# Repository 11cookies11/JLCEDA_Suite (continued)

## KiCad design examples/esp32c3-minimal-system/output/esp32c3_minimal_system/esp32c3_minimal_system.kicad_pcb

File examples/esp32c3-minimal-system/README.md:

# ESP32-C3 Minimal System

Verified example for the current KiCad Agent Suite project protocol.

This project models an ESP32-C3 minimum system board with 5 V input, 3.3 V
regulation, USB-C power and data, boot and reset controls, status LED, and GPIO
expansion headers.

## Source Of Truth

Edit this file only:

```text
source/circuit-model.source.json
```

Generated files are kept for inspection and KiCad handoff:

```text
output/esp32c3_minimal_system/
```

Do not edit generated `build/`, `output/`, or `project.state.json` files manually.

## Rebuild

Run from this example directory:

```powershell
hwtool agent status --project .
hwtool agent inspect --project .
hwtool agent resolve-symbols --project . --timeout 120
hwtool agent build-ir --project .
hwtool agent validate-ir --project .
hwtool agent export-kicad --project .
hwtool agent report --project . --markdown
hwtool agent diagnose --project .
```

## Current Verification

- `build-ir`: 17 components, 8 nets
- `validate-ir`: ok, 0 errors, 0 warnings
- `export-kicad`: generated schematic, PCB, ERC, and report artifacts
- `diagnose`: no must-fix issues

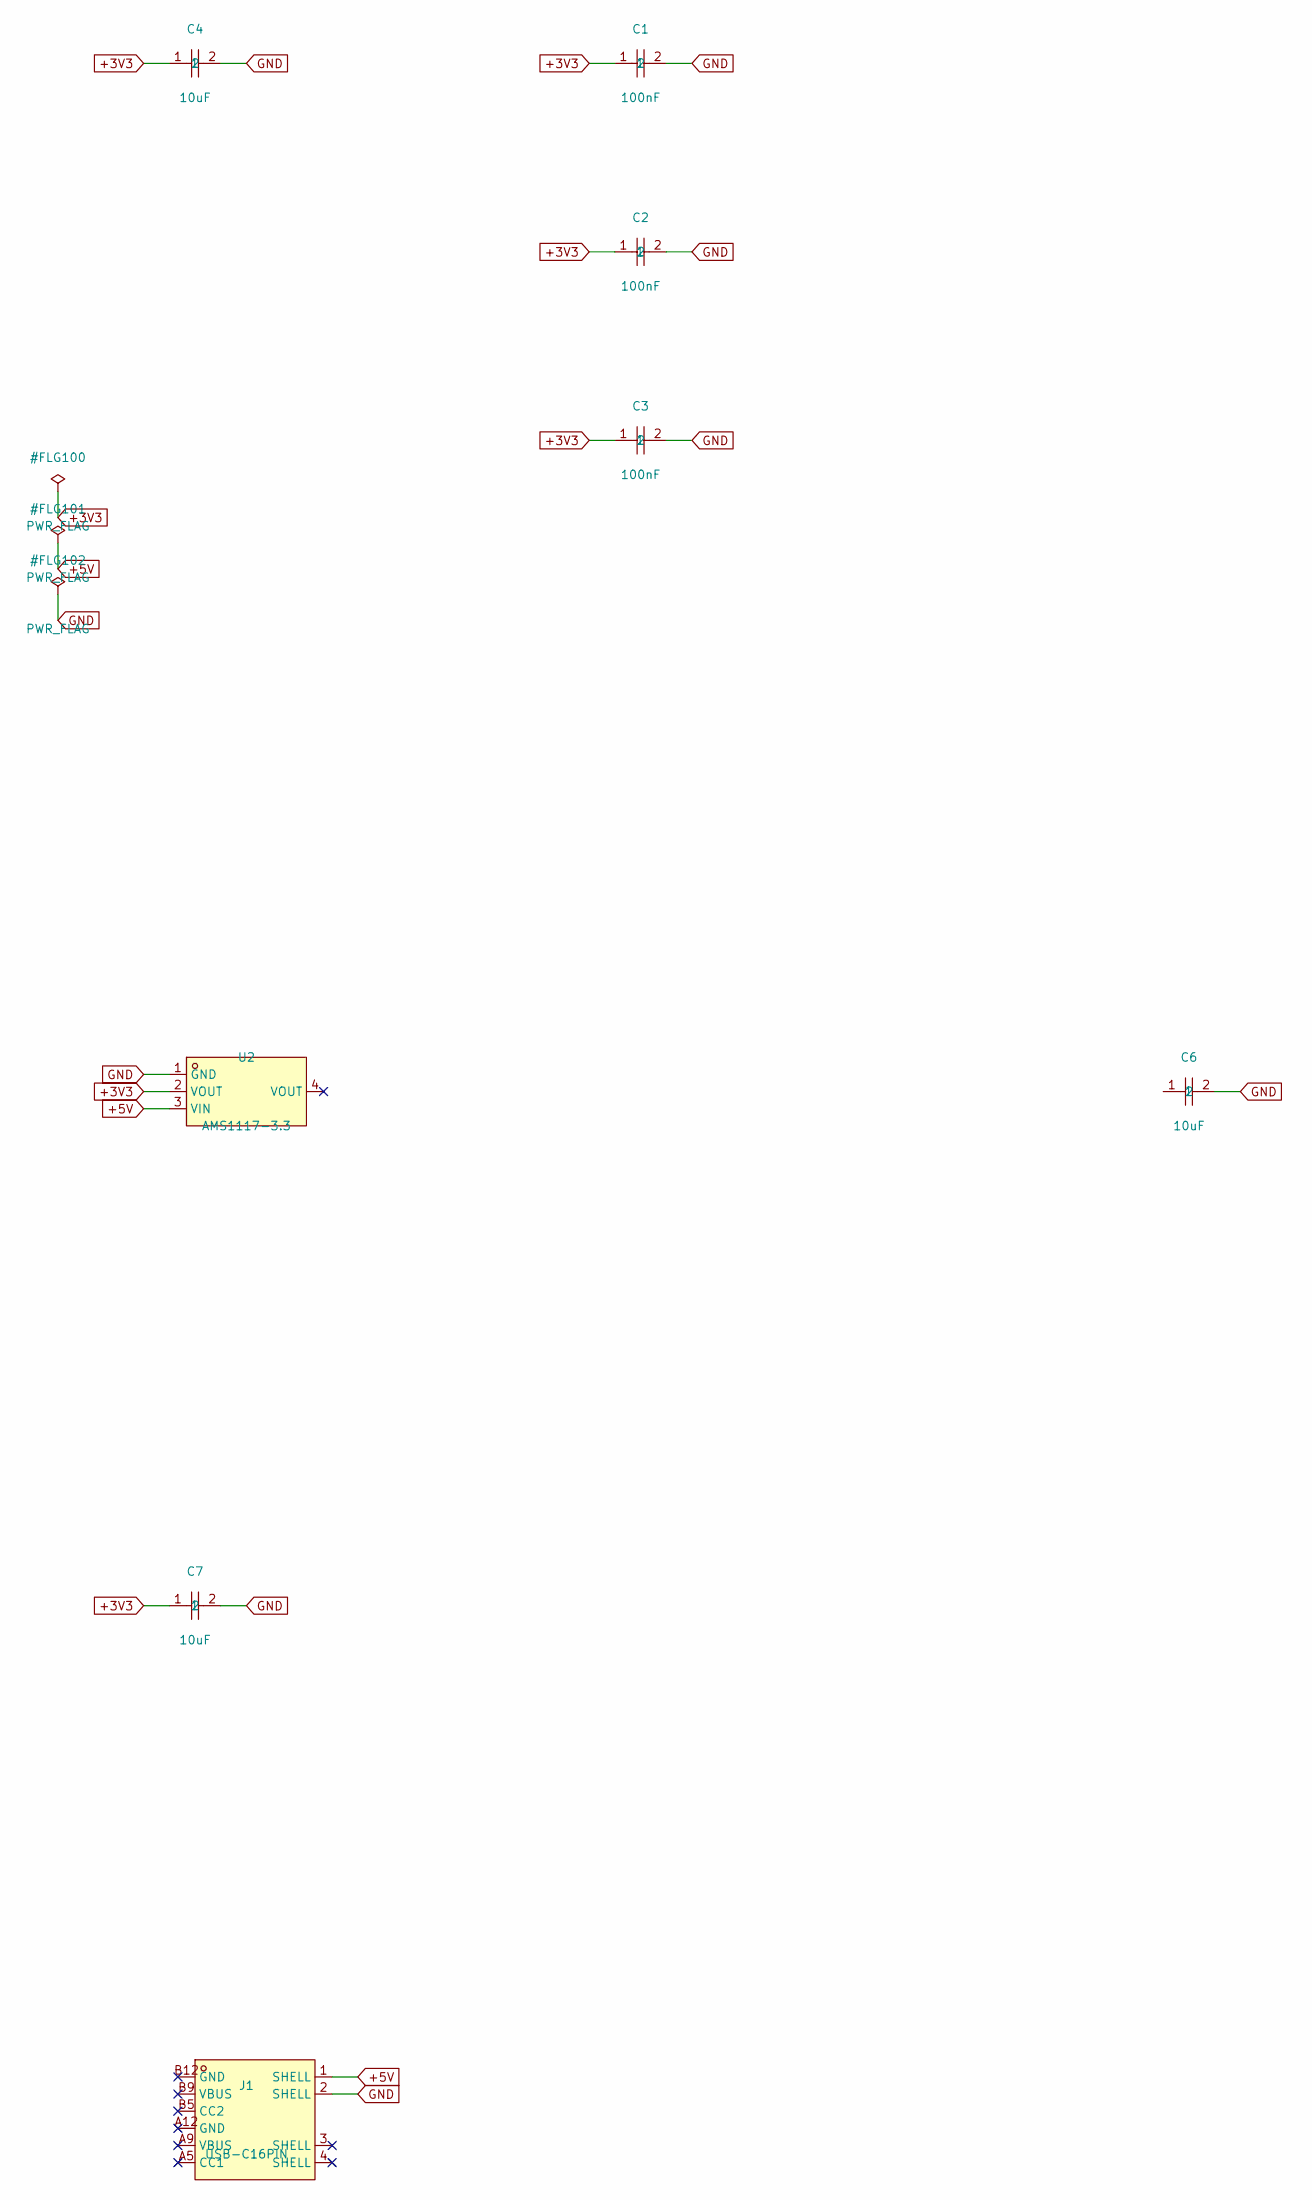
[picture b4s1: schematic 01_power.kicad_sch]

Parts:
C1, C2, C3: 100nF; C0603; LCSC C1590
C4, C6, C7: 10uF; C0805; LCSC C1713
J1: USB-C16PIN; USB-C-SMD_USB-TYPE-C-006; LCSC C2927026
U2: AMS1117-3.3; SOT-223-3_L6.5-W3.4-P2.30-LS7.0-BR; LCSC C6186

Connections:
+3V3: C1.1, C2.1, C3.1, C4.1, C7.1, U2.2 (VOUT); also elsewhere on the board
+5V: J1.1 (SHELL), U2.3 (VIN)
GND: C1.2, C2.2, C3.2, C4.2, C6.2, C7.2, J1.2 (SHELL), U2.1 (GND); also elsewhere on the board

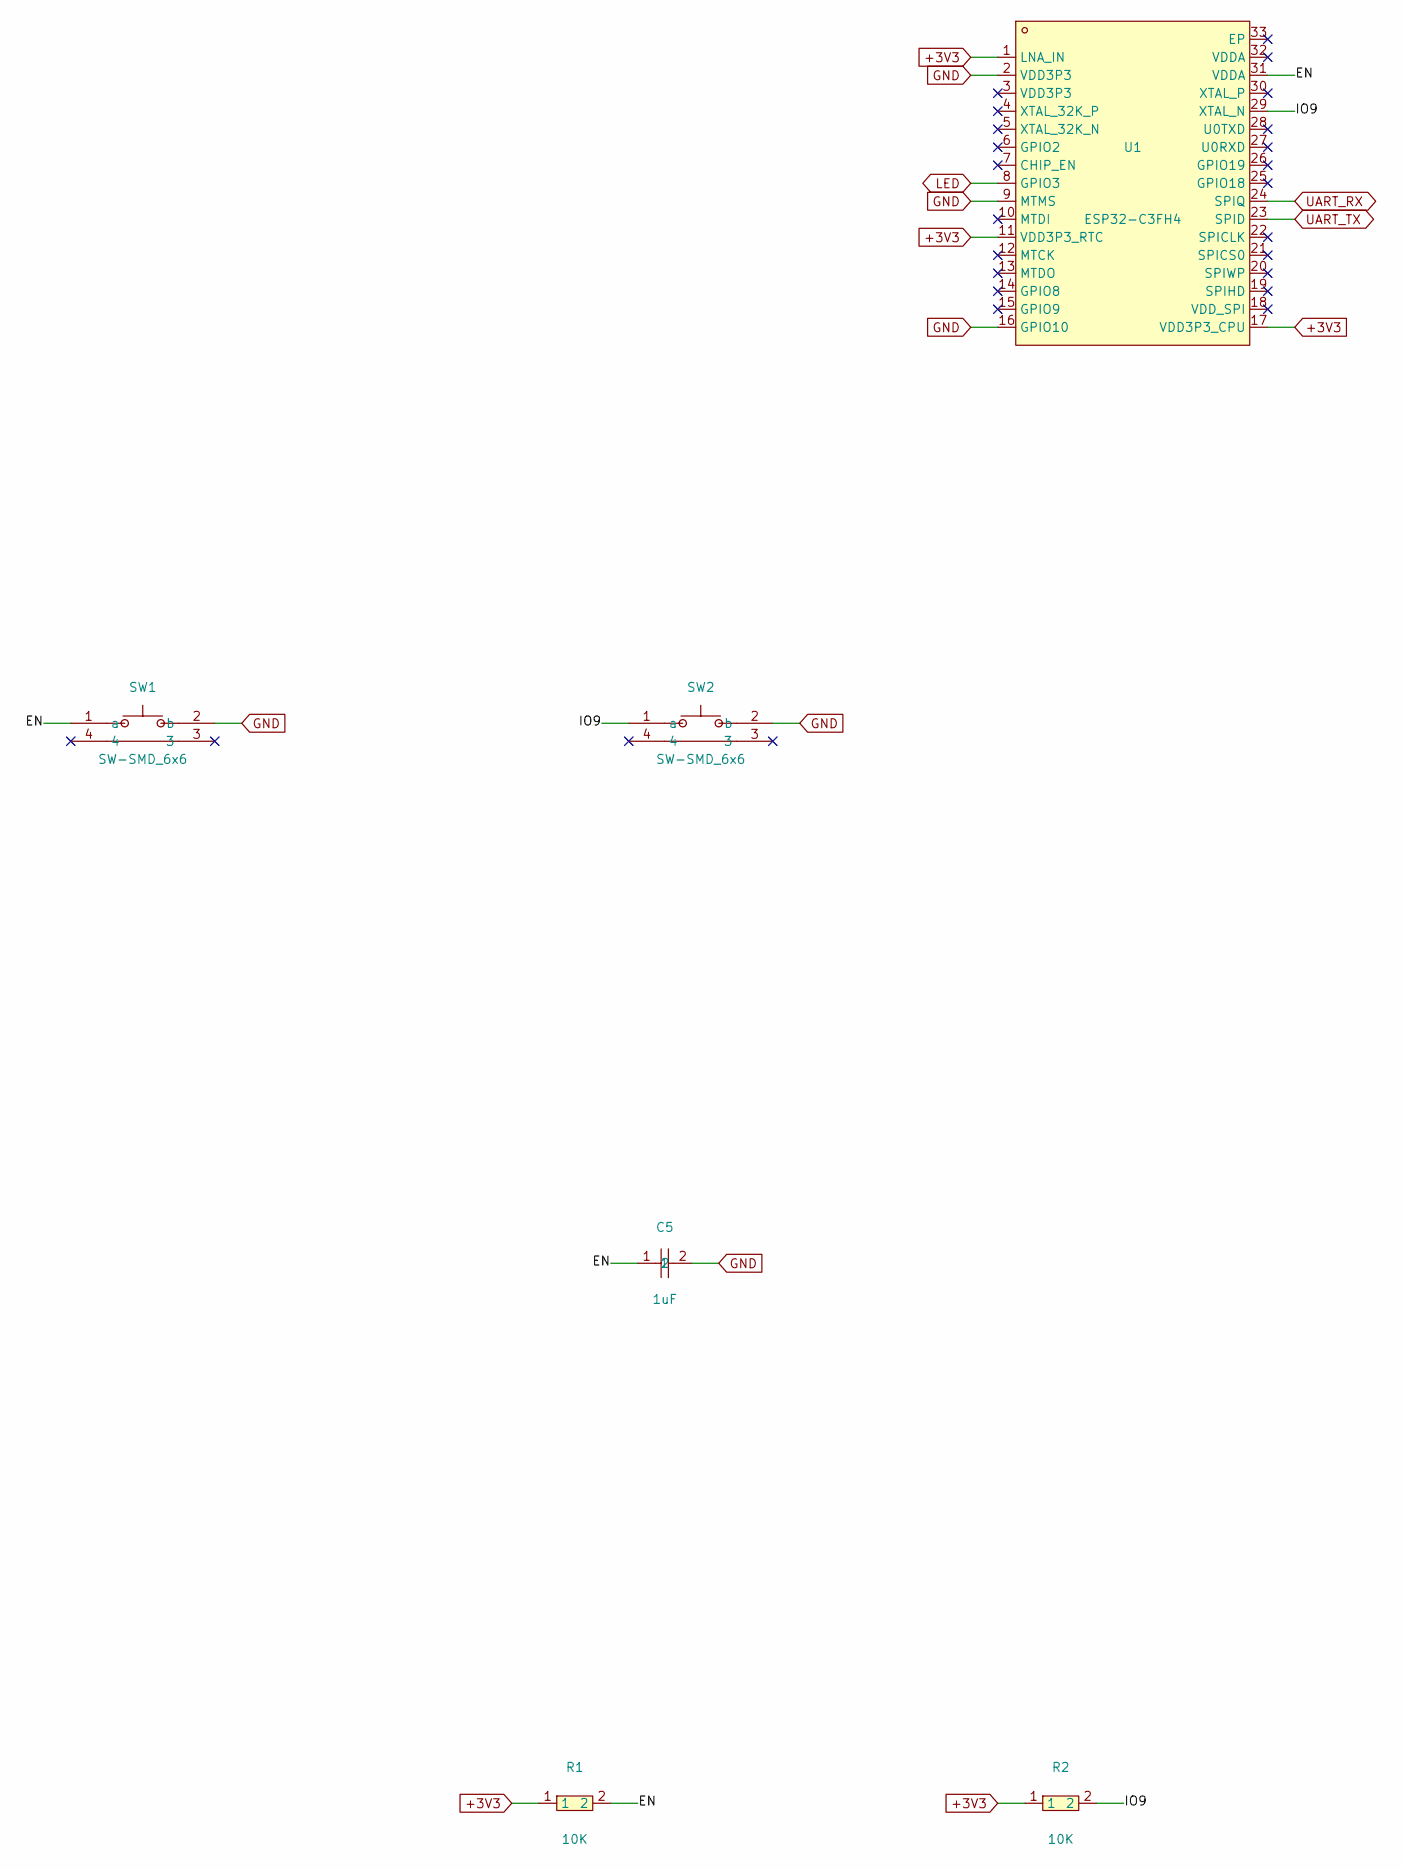
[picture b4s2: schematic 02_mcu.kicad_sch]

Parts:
C5: 1uF; C0603; LCSC C1592
R1, R2: 10K; R0603; LCSC C15401
SW1, SW2: SW-SMD_6x6; SW-SMD_K5-1617SA-02; LCSC C128964
U1: ESP32-C3FH4; QFN-32_L5.0-W5.0-P0.50-TL-EP3.7; LCSC C2858491

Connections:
+3V3: R1.1, R2.1, U1.1 (LNA_IN), U1.11 (VDD3P3_RTC), U1.17 (VDD3P3_CPU); also elsewhere on the board
EN: C5.1, R1.2, SW1.1 (a), U1.31 (VDDA)
GND: C5.2, SW1.2 (b), SW2.2 (b), U1.2 (VDD3P3), U1.9 (MTMS), U1.16 (GPIO10); also elsewhere on the board
IO9: R2.2, SW2.1 (a), U1.29 (XTAL_N)
LED: U1.8 (GPIO3); also elsewhere on the board
UART_RX: U1.24 (SPIQ); also elsewhere on the board
UART_TX: U1.23 (SPID); also elsewhere on the board

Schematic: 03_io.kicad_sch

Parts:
D1: LED0603; LED-SMD_L1.6-W0.8-RD_GREEN-1; LCSC C5139863
J2: UART-4P; HDR-TH_4P-P2.54-H-M-W10.4; LCSC C91552
R3: 1K; R0603; LCSC C14676

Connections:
+3V3: D1.1 (K), J2.1; also elsewhere on the board
GND: D1.2 (A), J2.4, R3.2; also elsewhere on the board
LED: R3.1; also elsewhere on the board
UART_RX: J2.3; also elsewhere on the board
UART_TX: J2.2; also elsewhere on the board

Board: 2 copper layers, 17 parts (0 on the bottom side), 8 nets, no tracks yet.

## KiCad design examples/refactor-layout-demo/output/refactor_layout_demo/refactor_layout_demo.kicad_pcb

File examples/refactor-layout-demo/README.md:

# STM32 Minimal System Demo

This project is a smoke example for the refactored package layout using a
fresh STM32F103 minimum system board model.
It uses the current project structure:

- `source/circuit-model.source.json` is the editable source model.
- `build/ir.v1.json` is generated by `agent build-ir`.
- `build/ir-validation.json` is generated by `agent validate-ir`.
- `build/report.json` and `build/report.md` are generated by `agent report`.

Try it from the repository root:

```powershell
$env:PYTHONPATH = "src"
python -m kicad_suite.cli agent status --project examples/refactor-layout-demo
python -m kicad_suite.cli agent inspect --project examples/refactor-layout-demo
python -m kicad_suite.cli agent resolve-symbols --project examples/refactor-layout-demo --timeout 120
python -m kicad_suite.cli agent build-ir --project examples/refactor-layout-demo
python -m kicad_suite.cli agent validate-ir --project examples/refactor-layout-demo
python -m kicad_suite.cli agent export-kicad --project examples/refactor-layout-demo
python -m kicad_suite.cli agent report --project examples/refactor-layout-demo --markdown
```

The board includes the minimum-system blocks:

- STM32F103C8T6 in LQFP-48
- AMS1117-3.3 regulator with input/output capacitors
- 8 MHz HSE crystal and load capacitors
- BOOT0 pull-down and NRST pull-up/reset button
- SWD header
- 5 V power input header and power LED

The model is intentionally compact and built from scratch for this demo, but it
still exercises the new
`entrypoints`, `application_services`, `domain/core`, `orchestration`, and
`adapters` imports.

Generated KiCad output is written to
`output/refactor_layout_demo/refactor_layout_demo.kicad_pro`.
The current generated PCB contains all 17 footprints. ERC still reports pin type
findings from generated/JLC symbols, so treat ERC as an inspection report rather
than a fabrication gate until symbol pin-type normalization is improved.

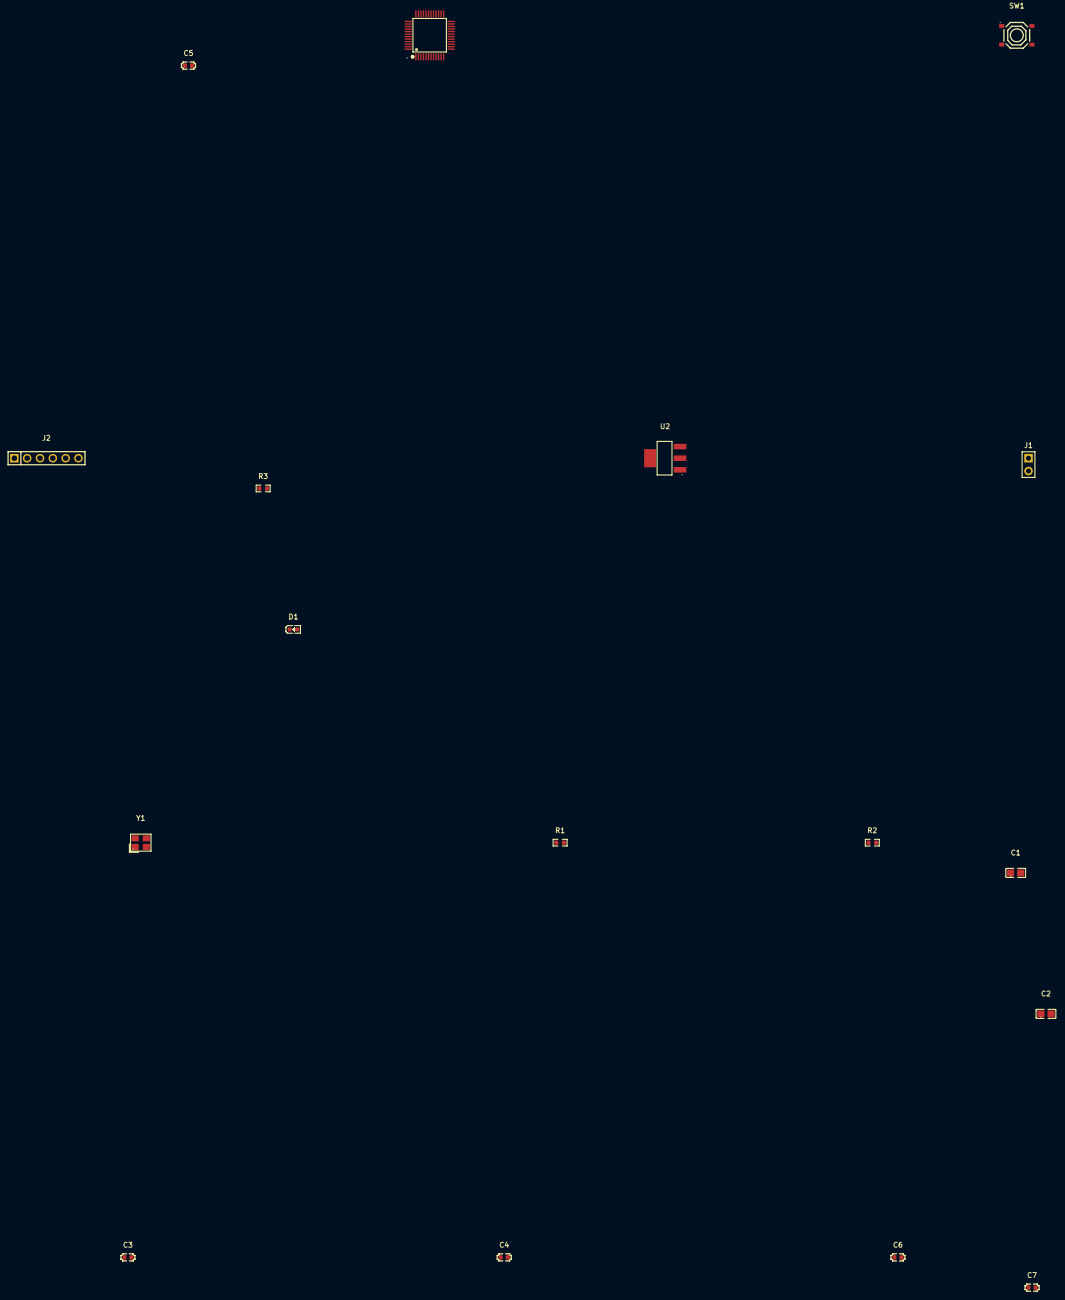
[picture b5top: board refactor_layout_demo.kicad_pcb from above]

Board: 2 copper layers, 17 parts (0 on the bottom side), 10 nets, no tracks yet.

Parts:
C1, C2: 10uF; C0805
C3, C4, C5: 100nF; C0603
C6, C7: 22pF; C0603
D1: Green LED; LED0603-RD
J1: 5V input; HDR-TH_2P-P2.54-V-M
J2: SWD 6-pin; HDR-TH_6P-P2.54-V-M
R1, R2: 10K; R0603
R3: 1K; R0603
SW1: Reset; SW-SMD_4P-L5.1-W5.1-P3.70-LS6.5-TL_H1.5
U1: STM32F103C8T6; LQFP-48_L7.0-W7.0-P0.50-LS9.0-BL
U2: AMS1117-3.3; SOT-223-3_L6.5-W3.4-P2.30-LS7.0-BR
Y1: 8MHz; CRYSTAL-SMD_4P-L3.2-W2.5-BL

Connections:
+3V3: C2.1, C3.1, C4.1, C5.1, J2.1, R1.1, R3.1, U1.1, U1.9, U1.24, U1.36, U1.48, U2.2
+5V: C1.1, J1.1, U2.3
BOOT0: R2.1, U1.44
GND: C1.2, C2.2, C3.2, C4.2, C5.2, C6.2, C7.2, D1.1, J1.2, J2.4, R2.2, SW1.2, U1.2, U1.8, U1.23, U1.35, U1.47, U2.1
HSE_IN: C6.1, U1.5, Y1.1
HSE_OUT: C7.1, U1.6, Y1.2
LED_A: D1.2, R3.2
NRST: J2.5, R1.2, SW1.1, U1.7
SWCLK: J2.3, U1.37
SWDIO: J2.2, U1.34

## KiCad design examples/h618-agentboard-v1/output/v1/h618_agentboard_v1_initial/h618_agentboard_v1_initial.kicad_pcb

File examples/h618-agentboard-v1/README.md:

# H618 AgentBoard V1

这是 H618 AgentBoard V1 示例项目的起始工作区。

## 项目目标

- 基于 Allwinner H618 设计一块低成本 Linux 控制板。
- 提供调试串口、MicroSD 启动、SPI NOR、以太网、USB Host 等基础能力。
- 面向 AI Agent 的硬件控制和日志采集工作流。

## 当前状态

- 需求已记录在 `docs/00_requirements.md`
- 系统架构已记录在 `docs/01_system_architecture.md`
- 电源树已记录在 `docs/02_power_tree.md`
- 启动流程已记录在 `docs/03_boot_flow.md`
- 引脚复用已记录在 `docs/04_pinmux.md`
- 原理图模块拆分已记录在 `docs/05_schematic_modules.md`
- PCB 约束已记录在 `docs/06_pcb_constraints.md`
- Bring-up 计划已记录在 `docs/07_bringup_plan.md`
- 风险清单已记录在 `docs/08_risks.md`
- 实施计划已记录在 `docs/09_implementation_plan.md`
- 拓扑完整度清单已记录在 `docs/10_topology_completeness_checklist.md`
- circuit-model 格式规范已记录在 `docs/11_circuit_model_format.md`
- 拓扑收口最后五项已记录在 `docs/12_topology_final_items.md`
- PMIC 收口方案已记录在 `docs/13_pmic_closure.md`
- DDR 收口方案已记录在 `docs/14_ddr_closure.md`
- SoC pinmap 收口方案已记录在 `docs/15_soc_pinmap_closure.md`
- 启动与恢复闭环方案已记录在 `docs/16_boot_recovery_closure.md`
- 接口收口方案已记录在 `docs/17_interface_closure.md`
- 原理图模块输入已记录在 `docs/18_schematic_module_inputs.md`
- 原理图分图元件与网络清单已记录在 `docs/19_schematic_sheet_parts_nets.md`
- 原理图捕获顺序已记录在 `docs/20_schematic_capture_order.md`
- 原理图捕获模板已记录在 `docs/21_schematic_capture_templates.md`
- ERC findings 分类已记录在 `docs/22_erc_findings_triage.md`
- 初始虚拟电路保存在 `source/circuit-model.source.json`
- 根目录 `libraries/` 已包含本项目的 EasyEDA/JLC 符号、封装和 3D 资产
- 初版原理图 pipeline 输出在 `output/v1/`
- KiCad 工程入口在 `output/v1/h618_agentboard_v1_initial/`

## 建议的推进顺序

1. 收口 `docs/00_requirements.md` 中的需求
2. 完成 `docs/01_system_architecture.md` 和 `docs/02_power_tree.md`
3. 按 `docs/09_implementation_plan.md` 继续推进
4. 用统一格式维护 `source/circuit-model.source.json`

## 相关入口

- [仓库根 README](../../README.md)
- [实施计划](docs/09_implementation_plan.md)
- [拓扑完整度清单](docs/10_topology_completeness_checklist.md)
- [circuit-model 格式规范](docs/11_circuit_model_format.md)
- [拓扑收口最后五项](docs/12_topology_final_items.md)
- [PMIC 收口方案](docs/13_pmic_closure.md)
- [DDR 收口方案](docs/14_ddr_closure.md)
- [SoC pinmap 收口方案](docs/15_soc_pinmap_closure.md)
- [启动与恢复闭环方案](docs/16_boot_recovery_closure.md)
- [接口收口方案](docs/17_interface_closure.md)
- [原理图模块输入](docs/18_schematic_module_inputs.md)
- [原理图分图元件与网络清单](docs/19_schematic_sheet_parts_nets.md)
- [原理图捕获顺序](docs/20_schematic_capture_order.md)
- [原理图捕获模板](docs/21_schematic_capture_templates.md)
- [ERC findings 分类](docs/22_erc_findings_triage.md)
- [初版 KiCad 工程](output/v1/h618_agentboard_v1_initial/)

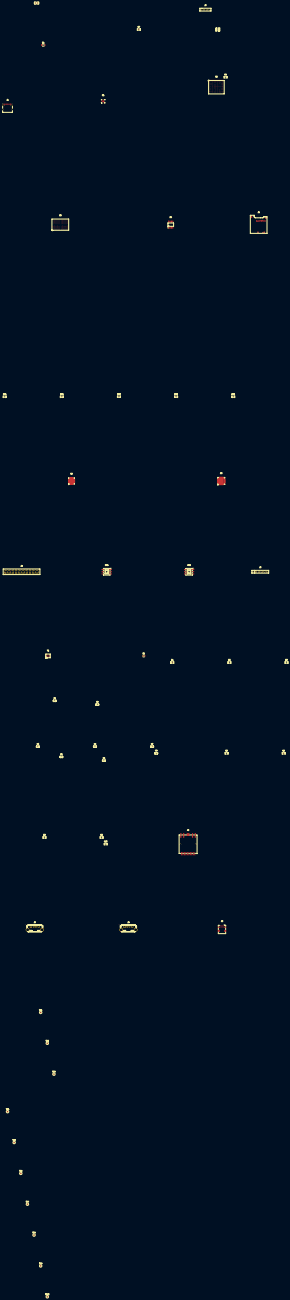
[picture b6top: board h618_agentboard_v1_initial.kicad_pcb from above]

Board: 2 copper layers, 55 parts (0 on the bottom side), 34 nets, no tracks yet.

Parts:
C1, C2: 18pF; C0603
C3, C4: 12pF; C0603
C5, C6, C7: 22uF; C0603
C8: 47uF; C0603
D1: 5V TVS clamp; SMF5.0A
F1: Resettable USB fuse; F0805
J1: USB-C 5V input; USB-C-SMD_TYPE-C16PIN
J2: MicroSD boot slot; TF-SMD_XKTF-001A
J3: UART0 debug header; HDR-TH_4P-P2.54-V-M-1
J4: 26-pin expansion header; HDR-TH_26P-P2.54-V-M-R2-C13-S2.54
J5: Future RP2040 / ESP32-class co-processor header; HDR-TH_6P-P2.54-V-M-1
J6: RJ45 with magnetics; RJ45-SMD_HC-RJ45-511Q-1-2
J7: USB-A host port 1; USB-A-TH_USB-A1VSB6
J8: USB-A host port 2; USB-A-TH_USB-A1VSB6
J9: Micro HDMI; TEPE-C-SMD_19P-P0.40
LED1: POWER; LED0603-RD
R1, R2: 2.2k; R0603
R3, R7, R8, R9, R10: 10k; R0603
R4: 1k; R0603
R5, R6: 5.1k; R0603
R11, R12, R13, R14, R15: 47k; R0603
SW1: RESET; SW-SMD_TK-6580S-2
SW2: FEL / BOOT; SW-SMD_TK-6580S-2
TP1: +5V_IN; TP-SMD_1P
TP2: +3V3; TP-SMD_1P
TP3: +1V8; TP-SMD_1P
TP4: +1V1_CORE; TP-SMD_1P
TP5: H618_UART0_TX; TP-SMD_1P
TP6: H618_UART0_RX; TP-SMD_1P
TP7: H618_RESET_N; TP-SMD_1P
TP8: H618_FEL_BOOT; TP-SMD_1P
TP9: +1V2_DDR; TP-SMD_1P
TP10: +0V9_DDR; TP-SMD_1P
U1: AXP313A or equivalent; QFN-20_L3.0-W3.0-P0.40-BL-EP1.7
U2: Allwinner H618; BGA-284_L14.0-W12.0-P0.65-TL
U3: 2GB LPDDR4; FBGA-200_L15.0-W10.0-BL_H9HCNNNBKUMLXR
U4: 16MB SPI NOR; SOP-8_L4.9-W3.9-P1.27-LS6.0-BL
U5: Gigabit PHY; WQFN-40_L5.0-W5.0-P0.4-BL-EP
U6: USB2.0 hub controller; VQFN-36_L6.0-W6.0-P0.50-BL-EP
Y1: 24MHz crystal; CRYSTAL-SMD_4P-L3.2-W2.5-BL
Y2: 32.768kHz crystal; CRYSTAL-SMD_3215-2P-L3.2-W1.5

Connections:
+0V9_DDR: TP10.1, U1.8
+1V1_CORE: C8.1, TP4.1, U1.12
+1V2_DDR: TP9.1, U1.1
+1V8: C7.1, TP3.1, U1.15
+3V3: C6.1, J2.4, J3.4, J4.1, J4.17, J5.2, R1.1, R2.1, R3.1, R7.1, R8.1, R9.1, R10.1, R11.1, R12.1, R13.1, R14.1, R15.1, TP2.1, U1.16, U4.8, U5.11, U5.29, U5.40, U6.5, U6.10, U6.15, U6.23, U6.29, U6.36
+5V_IN: D1.1, F1.1, J1.A4B9, J1.B4A9, TP1.1
+5V_SYS: C5.1, F1.2, J4.2, J4.4, LED1.1, R4.1, U1.17
GND: C1.2, C2.2, C3.2, C4.2, C5.2, C6.2, C7.2, C8.2, D1.2, J1.1, J1.2, J1.3, J1.4, J1.A1B12, J1.B1A12, J2.6, J2.10, J2.11, J2.12, J2.13, J3.1, J4.6, J4.9, J4.14, J4.20, J4.25, J5.1, J6.1, J7.1, J8.1, J9.5, J9.6, J9.7, J9.8, LED1.2, R4.2, R5.2, R6.2, SW1.1, SW2.1, U1.9, U3.A3, U4.4, U5.41, U6.37, Y1.2, Y1.4
H618_24M_XIN: C1.1, Y1.1
H618_24M_XOUT: C2.1, Y1.3
H618_32K_XIN: C3.1, Y2.1
H618_32K_XOUT: C4.1, Y2.2
H618_COPRO_UART: J5.3, J5.4
H618_FEL_BOOT: R8.2, SW2.2, TP8.1
H618_HDMI: J9.1, J9.2, J9.3, J9.4
H618_PMIC_I2C_SCL: R1.2, U1.6
H618_PMIC_I2C_SDA: R2.2, U1.5
H618_PMIC_PWRON: R3.2, U1.14
H618_RESET_N: R7.2, SW1.2, TP7.1
H618_SD_CMD: J2.3, R11.2
H618_SD_D0: J2.7, R12.2
H618_SD_D1: J2.8, R13.2, U2.D1
H618_SD_D2: J2.1, R14.2, U2.D2
H618_SD_D3: J2.2, R15.2, U2.D3
H618_SPI0_HOLD_N: R10.2, U4.7
H618_SPI0_WP_N: R9.2, U4.3
H618_UART0_RX: J3.3, TP6.1
H618_UART0_TX: J3.2, TP5.1
USB_C_CC1: J1.A5, R5.1
USB_C_CC2: J1.B5, R6.1
USB_HUB_PORT1_DM: J7.2, U6.1
USB_HUB_PORT1_DP: J7.3, U6.2
USB_HUB_PORT2_DM: J8.2, U6.3
USB_HUB_PORT2_DP: J8.3, U6.4

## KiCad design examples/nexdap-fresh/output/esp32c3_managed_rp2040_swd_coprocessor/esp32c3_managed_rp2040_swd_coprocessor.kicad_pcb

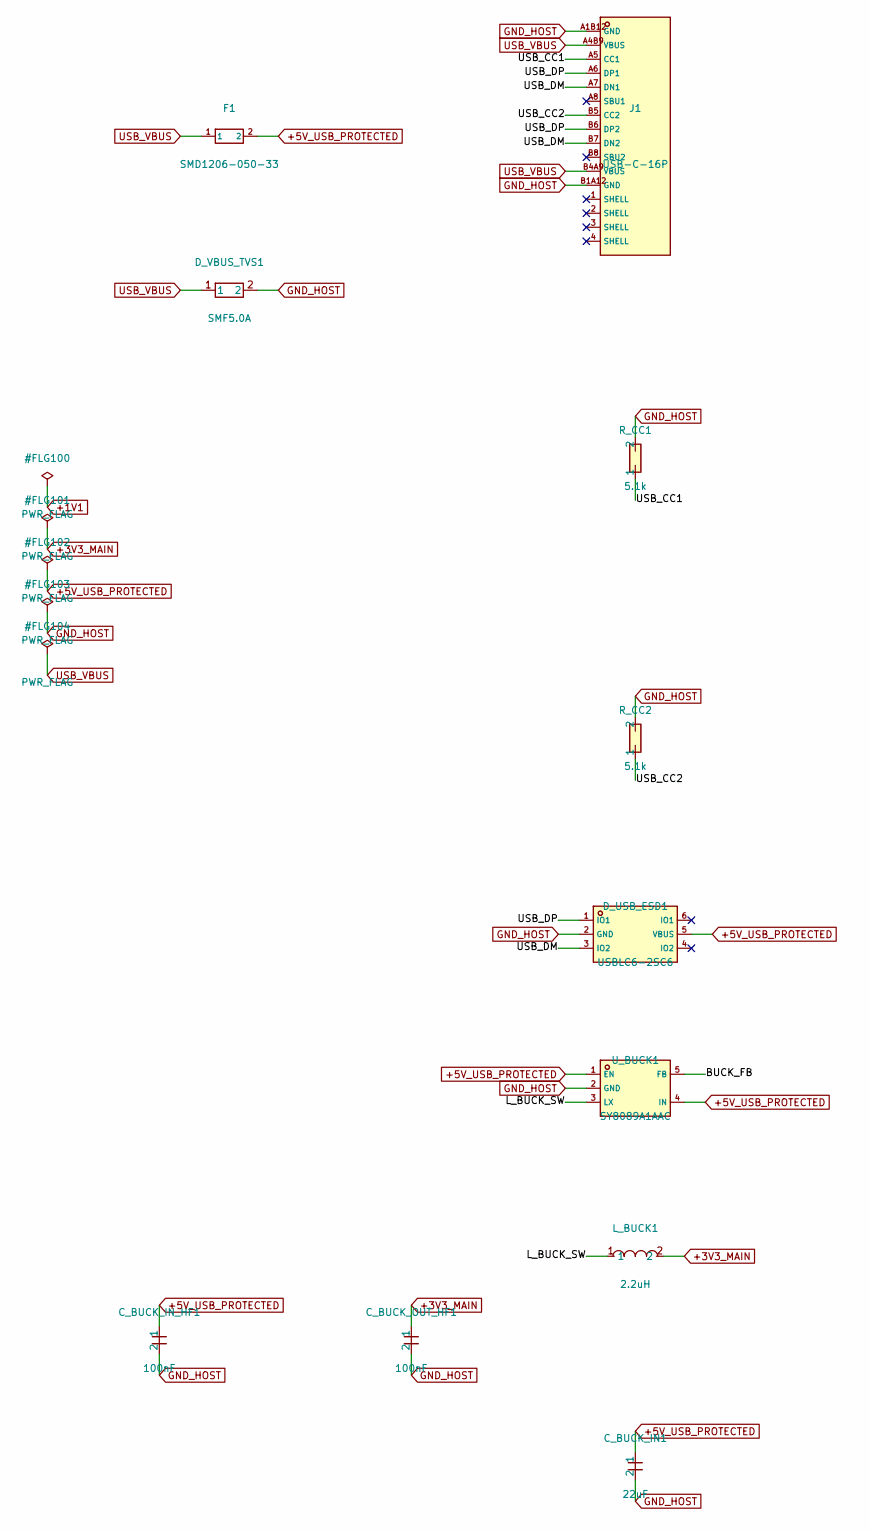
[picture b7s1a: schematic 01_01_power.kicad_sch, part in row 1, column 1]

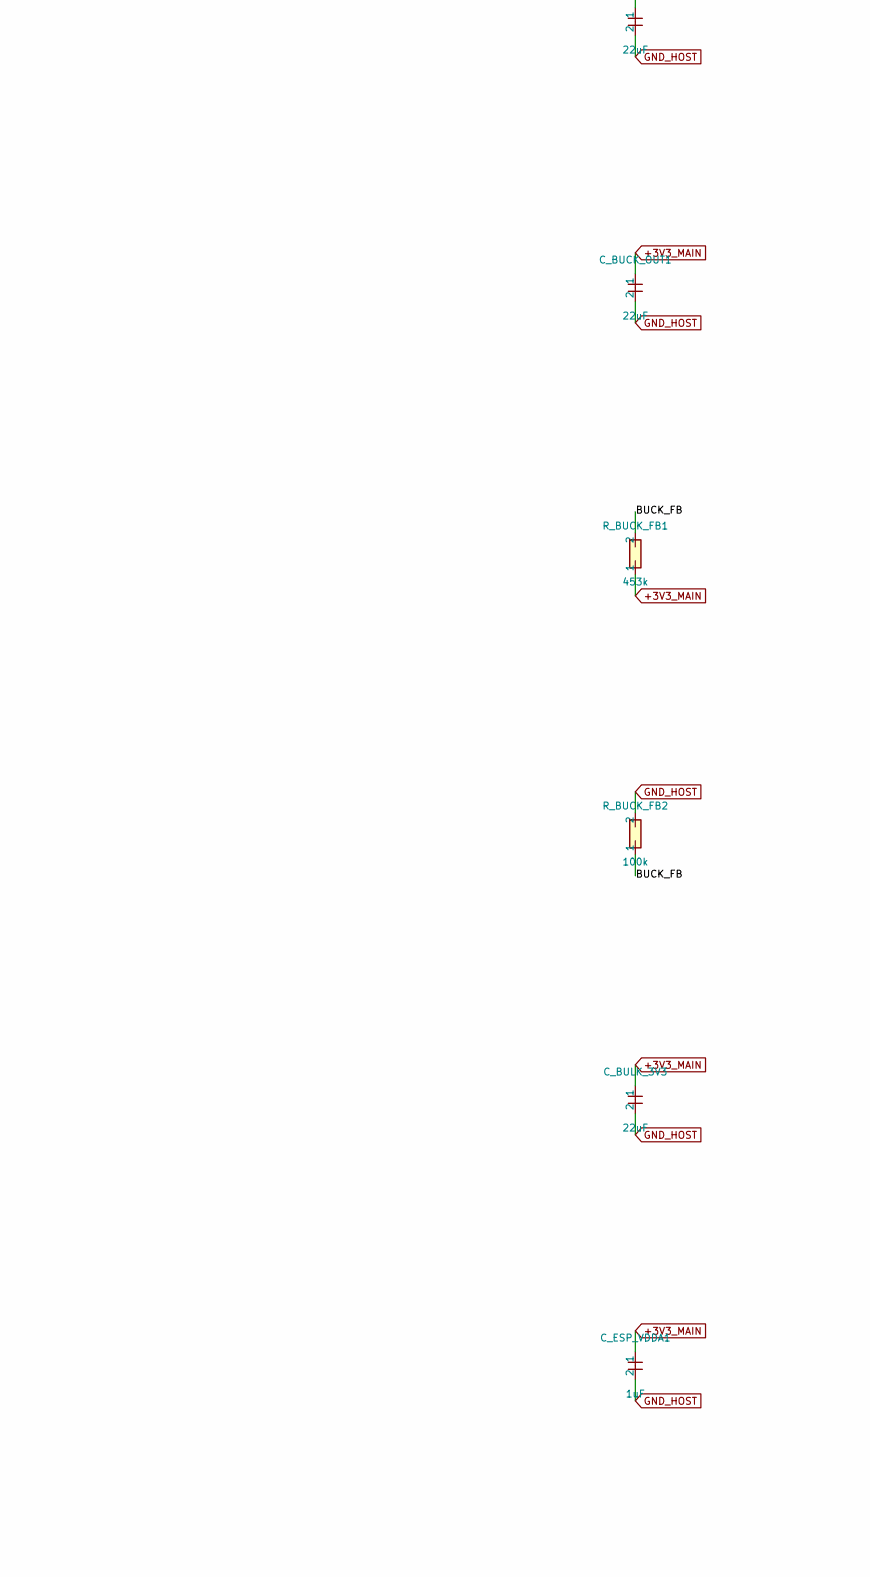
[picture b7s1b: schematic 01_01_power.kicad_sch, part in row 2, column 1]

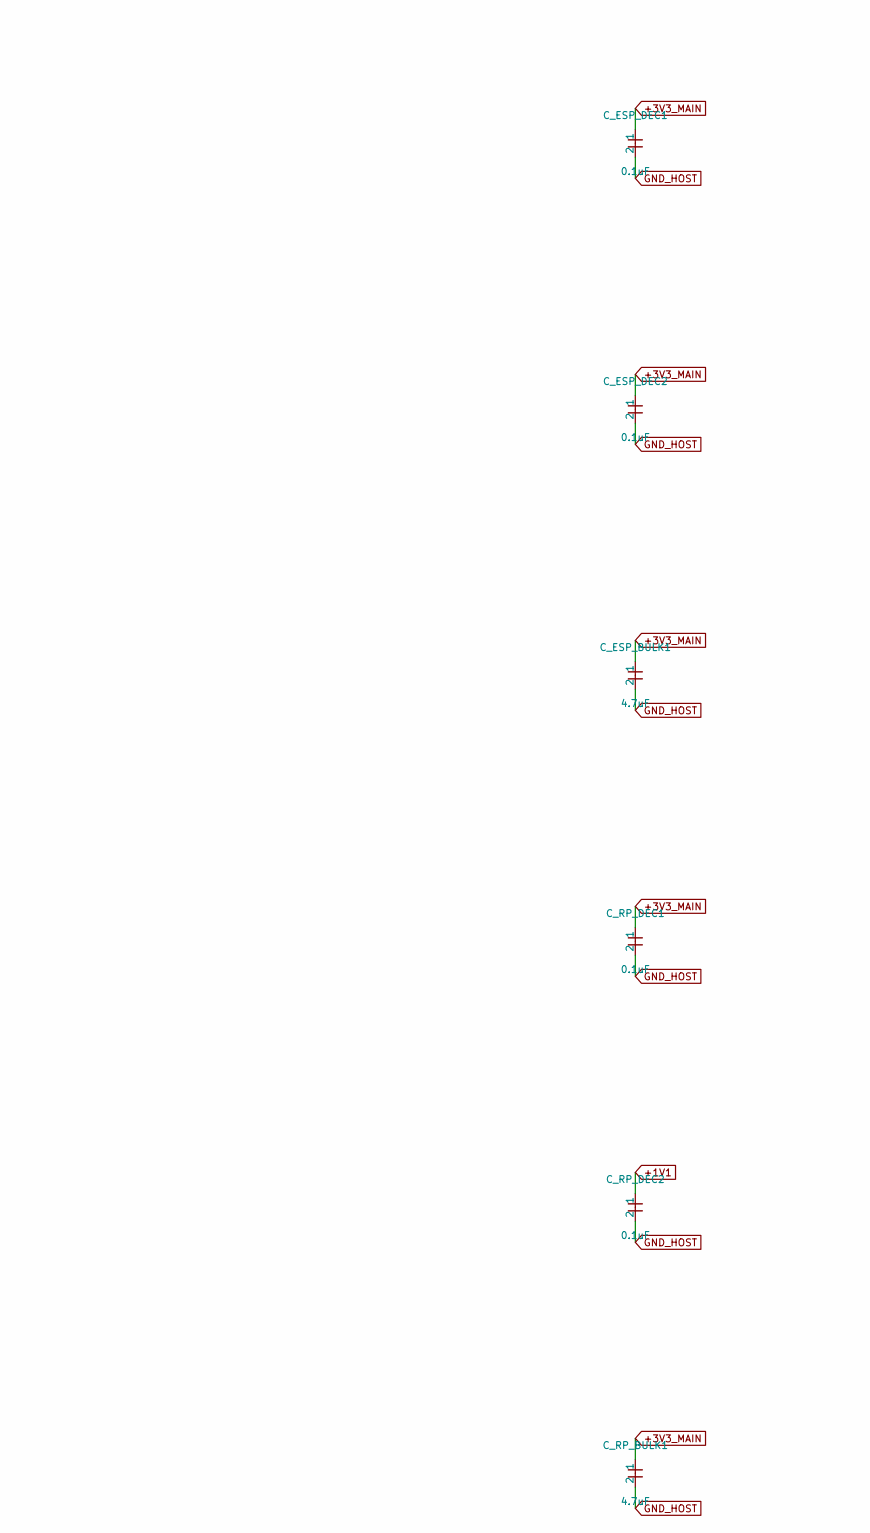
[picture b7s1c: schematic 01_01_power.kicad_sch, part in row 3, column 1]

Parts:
C_BUCK_IN1: 22uF; C0603
C_BUCK_IN_HF1: 100nF; C0603
C_BUCK_OUT1: 22uF; C0603
C_BUCK_OUT_HF1: 100nF; C0603
C_BULK_3V3: 22uF; C0603
C_ESP_BULK1: 4.7uF; C0603
C_ESP_DEC1, C_ESP_DEC2: 0.1uF; C0603
C_ESP_VDDA1: 1uF; C0603
C_RP_BULK1: 4.7uF; C0603
C_RP_DEC1, C_RP_DEC2: 0.1uF; C0603
D_USB_ESD1: USBLC6-2SC6; SOT-23-6_L2.9-W1.6-P0.95-LS2.8-BL
D_VBUS_TVS1: SMF5.0A
F1: SMD1206-050-33
J1: USB-C-16P; USB-C-SMD_TYPE-C16PIN
L_BUCK1: 2.2uH; L0805; MPN APH201208C2R2MP03; LCSC C42455262
R_BUCK_FB1: 453k; R0603
R_BUCK_FB2: 100k; R0603
R_CC1, R_CC2: 5.1k; R0603
U_BUCK1: SY8089A1AAC; TSOT-23-5_L2.9-W1.6-P0.95-LS2.8-BR

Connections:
+1V1: C_RP_DEC2.1; also elsewhere on the board
+3V3_MAIN: C_BUCK_OUT1.1, C_BUCK_OUT_HF1.1, C_BULK_3V3.1, C_ESP_BULK1.1, C_ESP_DEC1.1, C_ESP_DEC2.1, C_ESP_VDDA1.1, C_RP_BULK1.1, C_RP_DEC1.1, L_BUCK1.2, R_BUCK_FB1.1; also elsewhere on the board
+5V_USB_PROTECTED: C_BUCK_IN1.1, C_BUCK_IN_HF1.1, D_USB_ESD1.5 (VBUS), F1.2, U_BUCK1.1 (EN), U_BUCK1.4 (IN); also elsewhere on the board
/01_power/BUCK_FB: R_BUCK_FB1.2, R_BUCK_FB2.1, U_BUCK1.5 (FB)
/01_power/L_BUCK_SW: L_BUCK1.1, U_BUCK1.3 (LX)
/01_power/USB_CC1: J1.A5 (CC1), R_CC1.1
/01_power/USB_CC2: J1.B5 (CC2), R_CC2.1
/01_power/USB_DM: D_USB_ESD1.3 (IO2), J1.A7 (DN1), J1.B7 (DN2)
/01_power/USB_DP: D_USB_ESD1.1 (IO1), J1.A6 (DP1), J1.B6 (DP2)
GND_HOST: C_BUCK_IN1.2, C_BUCK_IN_HF1.2, C_BUCK_OUT1.2, C_BUCK_OUT_HF1.2, C_BULK_3V3.2, C_ESP_BULK1.2, C_ESP_DEC1.2, C_ESP_DEC2.2, C_ESP_VDDA1.2, C_RP_BULK1.2, C_RP_DEC1.2, C_RP_DEC2.2, D_USB_ESD1.2 (GND), D_VBUS_TVS1.2, J1.A1B12 (GND), J1.B1A12 (GND), R_BUCK_FB2.2, R_CC1.2, R_CC2.2, U_BUCK1.2 (GND); also elsewhere on the board
USB_VBUS: D_VBUS_TVS1.1, F1.1, J1.A4B9 (VBUS), J1.B4A9 (VBUS)
